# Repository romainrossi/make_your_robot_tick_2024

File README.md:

# Make Your Robot Tick 2024

Make Your Robot Tick, a robotics competition by ESIGELEC and Muthoot.

# Asking Questions about the Competition

As a participating Team, if you have a question about the RuleBook or other aspect of the competition, you have to fill an issue in this repository.
1. Go to [Issues](../../issues)  and check if your question is already answered
2. If not, create a new issue with the "New Issue" button, and fill-in the form of the "RuleBook question" template.
3. The organisation team will shortly answer your question. Question and answer will be available for all teams.

# Soon

Soon, all the information for this robotics competition will be available here.
Follow this repository to be notified !

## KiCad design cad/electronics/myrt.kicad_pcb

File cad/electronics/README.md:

# Make Your Robot Tick - Electronics CAD files

This directory contains a KiCAD project for the electronic boards used on the game field.

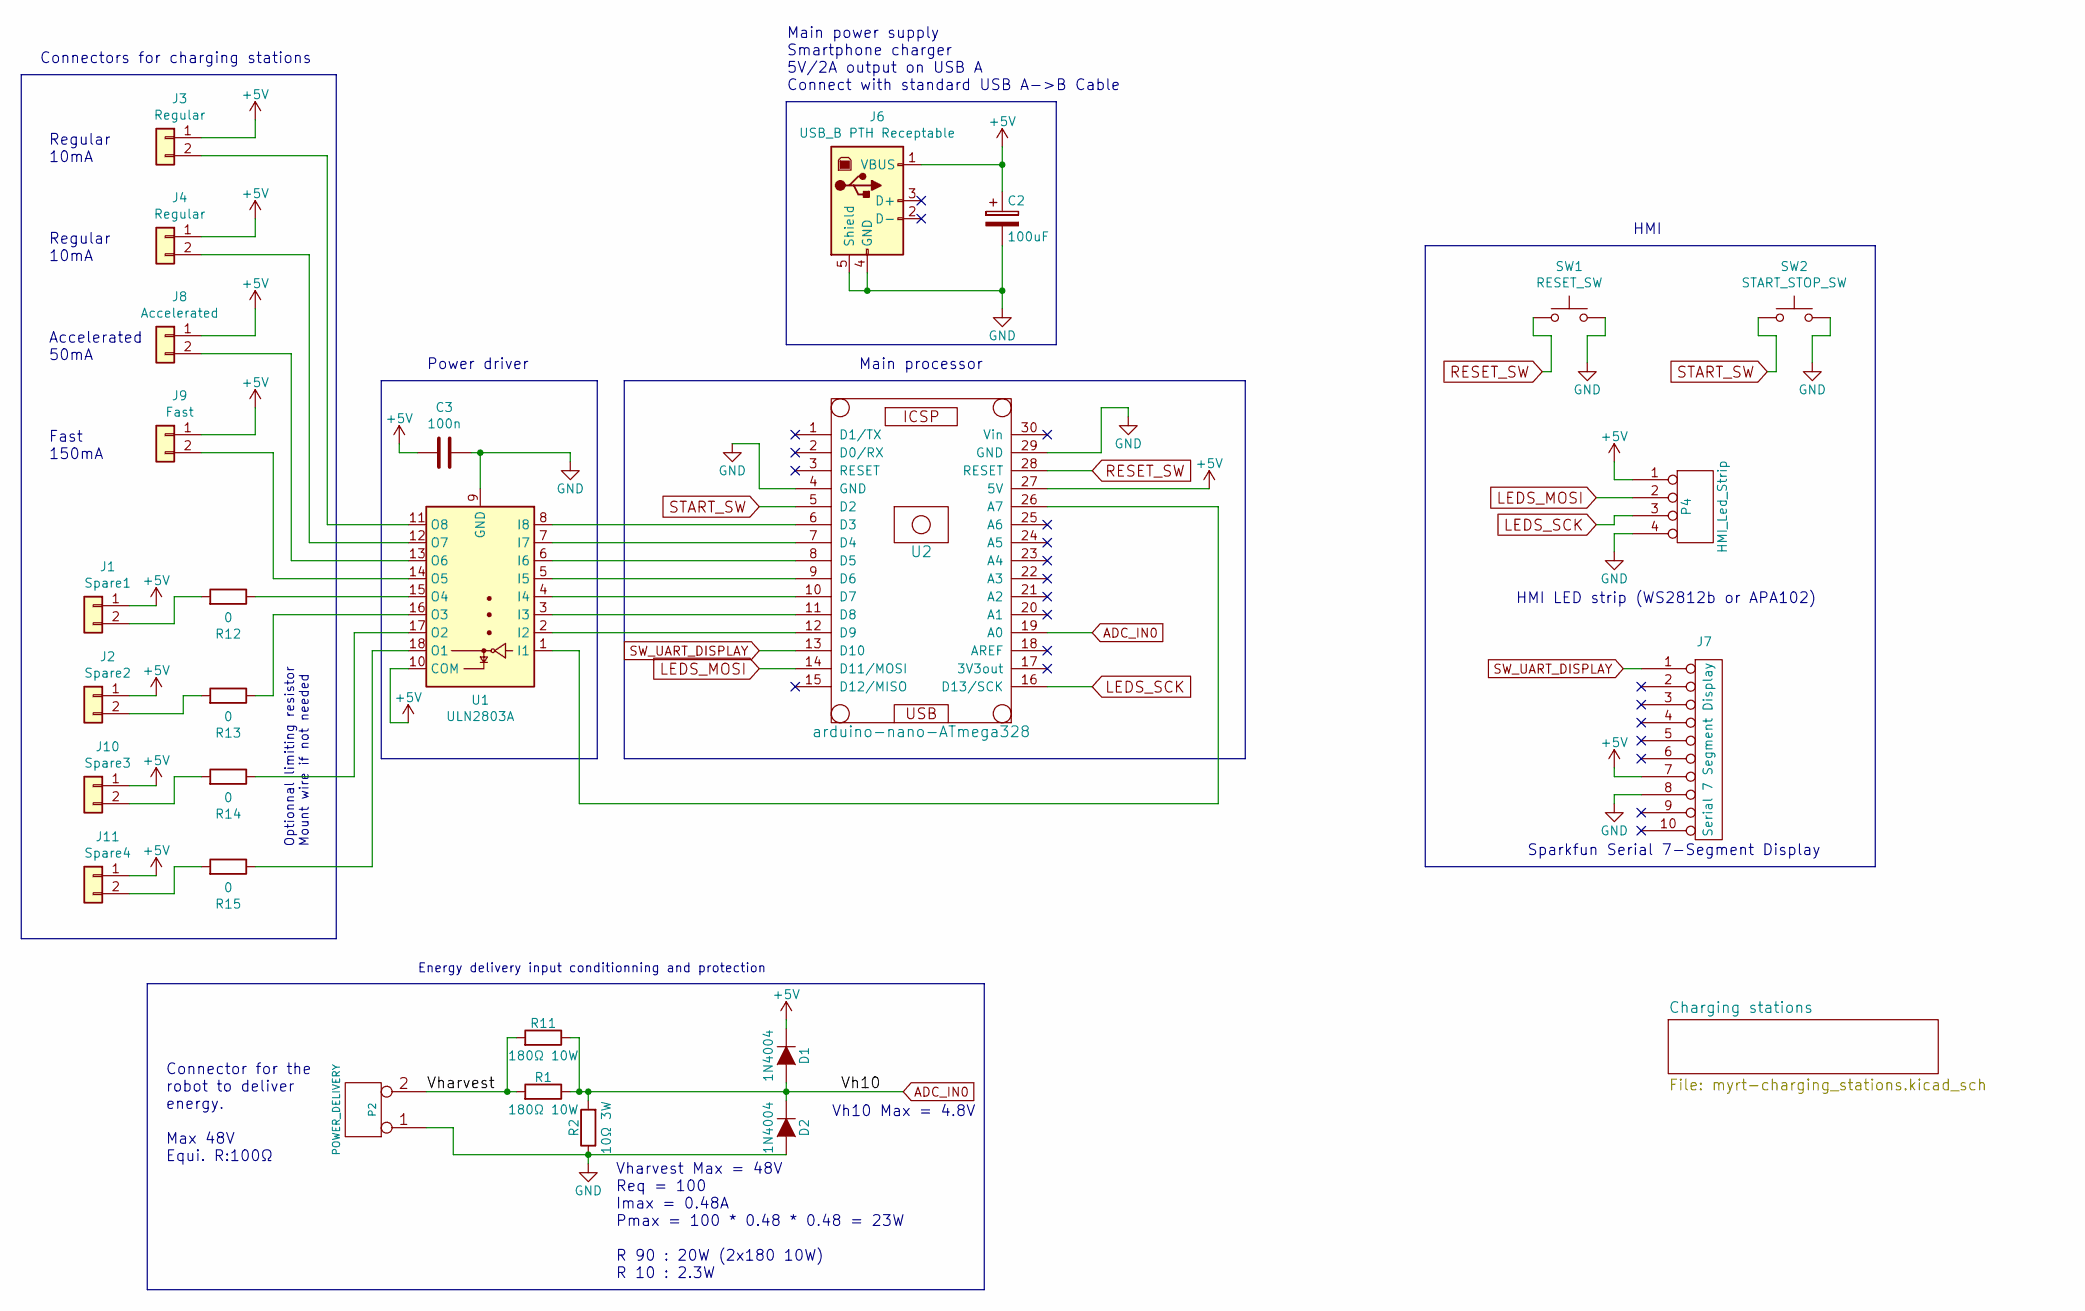
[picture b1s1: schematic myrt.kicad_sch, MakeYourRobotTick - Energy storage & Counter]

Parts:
C2: 100uF; CP_Radial_D10.0mm_P5.00mm
C3: 100n; C_Rect_L7.0mm_W2.5mm_P5.00mm
D1, D2: 1N4004; D_DO-41_SOD81_P12.70mm_Horizontal
J1: Spare1; PhoenixContact_MCV_1,5_2-G-3.5_1x02_P3.50mm_Vertical
J2: Spare2; PhoenixContact_MCV_1,5_2-G-3.5_1x02_P3.50mm_Vertical
J3, J4: Regular; PhoenixContact_MCV_1,5_2-G-3.5_1x02_P3.50mm_Vertical
J6: USB_B PTH Receptable; USB_B_OST_USB-B1HSxx_Horizontal
J7: Serial 7 Segment Display; PinSocket_1x10_P2.54mm_Vertical
J8: Accelerated; PhoenixContact_MCV_1,5_2-G-3.5_1x02_P3.50mm_Vertical
J9: Fast; PhoenixContact_MCV_1,5_2-G-3.5_1x02_P3.50mm_Vertical
J10: Spare3; PhoenixContact_MCV_1,5_2-G-3.5_1x02_P3.50mm_Vertical
J11: Spare4; PhoenixContact_MCV_1,5_2-G-3.5_1x02_P3.50mm_Vertical
P2: POWER_DELIVERY; PhoenixContact_MCV_1,5_2-G-3.5_1x02_P3.50mm_Vertical
P4: HMI_Led_Strip; PinSocket_1x04_P2.54mm_Vertical
R1, R11: 180Ω 10W; R_Axial_Power_L48.0mm_W12.5mm_P55.88mm
R2: 10Ω 3W; R_Axial_DIN0516_L15.5mm_D5.0mm_P25.40mm_Horizontal
R12, R13, R14, R15: 0; R_Axial_DIN0207_L6.3mm_D2.5mm_P15.24mm_Horizontal
SW1: RESET_SW; SW_PUSH-12mm_Wuerth-430476085716
SW2: START_STOP_SW; SW_PUSH-12mm_Wuerth-430476085716
U1: ULN2803A; DIP-18_W7.62mm_Socket_LongPads
U2: arduino-nano-ATmega328; Arduino_Nano

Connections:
+5V: C2.1, C3.2, D1.1 (K), J1.1, J2.1, J3.1, J4.1, J6.1 (VBUS), J7.7, J8.1, J9.1, J10.1, J11.1, P4.1, U1.10 (COM), U2.27 (5V)
/Vharvest: P2.2, R1.2, R11.2
ADC_IN0: D1.2 (A), D2.1 (K), R1.1, R2.2, R11.1, U2.19 (A0)
GND: C2.2, C3.1, D2.2 (A), J6.4 (GND), J6.5 (Shield), J7.8, P2.1, P4.4, R2.1, SW1.2, SW2.2, U1.9 (GND), U2.4 (GND), U2.29 (GND)
LEDS_MOSI: P4.2, U2.14 (D11/MOSI)
LEDS_SCK: P4.3, U2.16 (D13/SCK)
unnamed: J1.2, R12.2
unnamed: J2.2, R13.2
unnamed: J3.2, U1.11 (O8)
unnamed: J4.2, U1.12 (O7)
unnamed: J8.2, U1.13 (O6)
unnamed: J9.2, U1.14 (O5)
unnamed: J10.2, R14.2
unnamed: J11.2, R15.2
unnamed: R12.1, U1.15 (O4)
unnamed: R13.1, U1.16 (O3)
unnamed: R14.1, U1.17 (O2)
unnamed: R15.1, U1.18 (O1)
unnamed: U1.1 (I1), U2.26 (A7)
unnamed: U1.2 (I2), U2.12 (D9)
unnamed: U1.3 (I3), U2.11 (D8)
unnamed: U1.4 (I4), U2.10 (D7)
unnamed: U1.5 (I5), U2.9 (D6)
unnamed: U1.6 (I6), U2.8 (D5)
unnamed: U1.7 (I7), U2.7 (D4)
unnamed: U1.8 (I8), U2.6 (D3)
RESET_SW: SW1.1, U2.28 (RESET)
START_SW: SW2.1, U2.5 (D2)
SW_UART_DISPLAY: J7.1, U2.13 (D10)

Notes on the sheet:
Connector for the robot to deliver energy. Max 48V Equi. R:100Ω
Energy delivery input conditionning and protection
Optionnal limiting resistor Mount wire if not needed
Vharvest Max = 48V Req = 100 Imax = 0.48A Pmax = 100 * 0.48 * 0.48 = 23W R 90 : 20W (2x180 10W) R 10 : 2.3W
HMI
Main power supply Smartphone charger 5V/2A output on USB A Connect with standard USB A->B Cable
Power driver
Vh10 Max = 4.8V
Connectors for charging stations
Sparkfun Serial 7-Segment Display
HMI LED strip (WS2812b or APA102)
Accelerated 50mA
Regular 10mA
Fast 150mA
Main processor

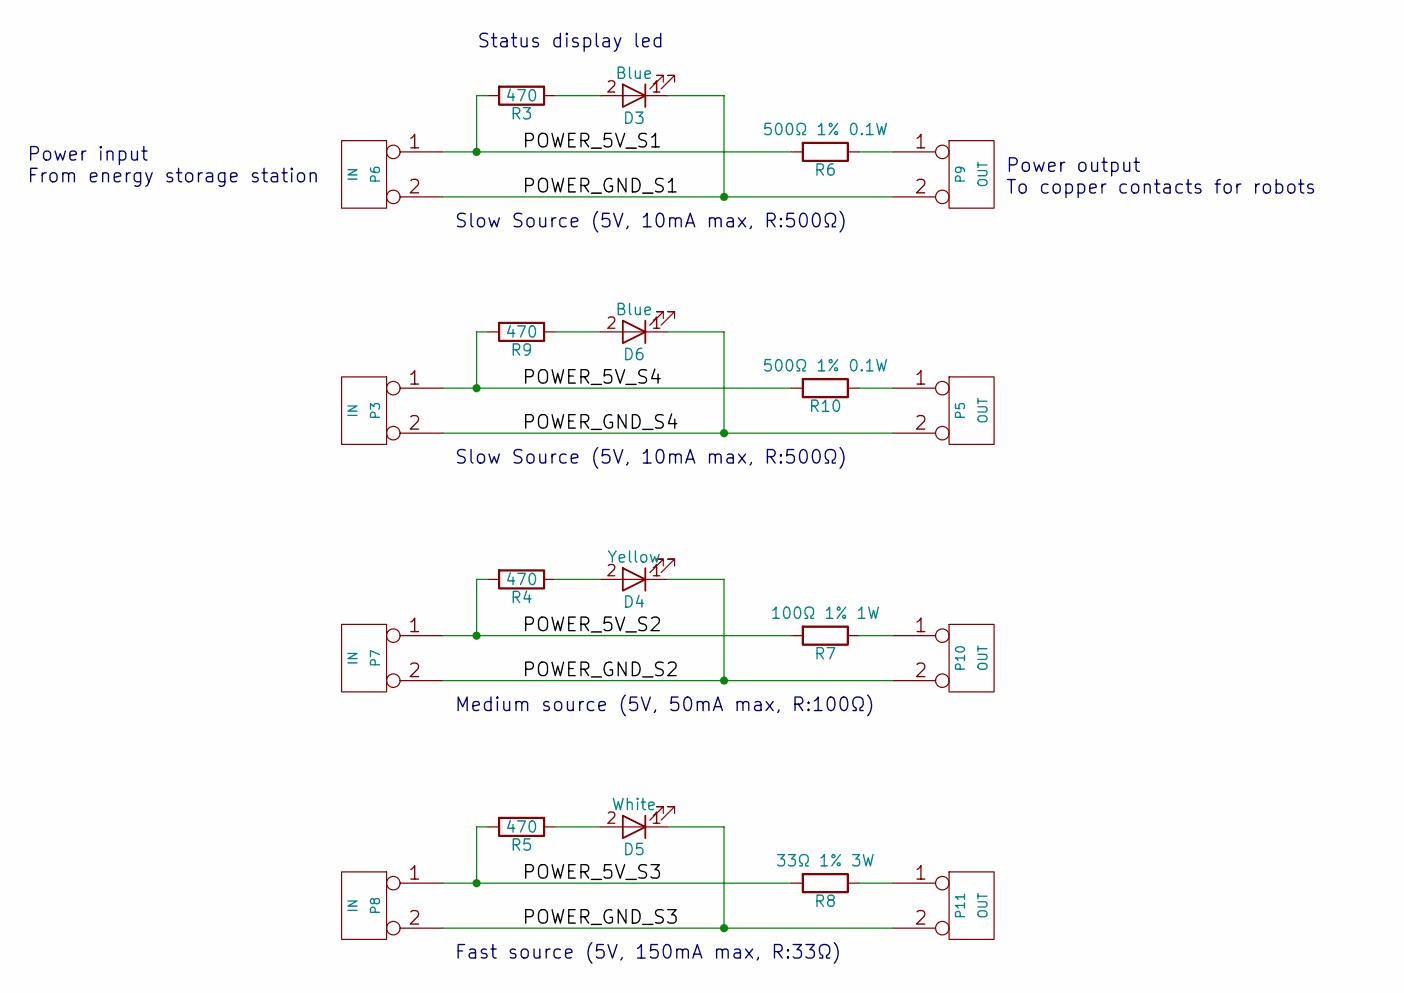
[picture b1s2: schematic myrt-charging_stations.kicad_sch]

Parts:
D3, D6: Blue; LED_D5.0mm
D4: Yellow; LED_D5.0mm
D5: White; LED_D5.0mm
P3, P6, P7, P8: IN; PhoenixContact_MCV_1,5_2-G-3.5_1x02_P3.50mm_Vertical
P5, P9, P10, P11: OUT; PinSocket_1x02_P2.54mm_Vertical
R3, R4, R5, R9: 470; R_Axial_DIN0207_L6.3mm_D2.5mm_P10.16mm_Horizontal
R6, R10: 500Ω 1% 0.1W; R_Axial_DIN0207_L6.3mm_D2.5mm_P15.24mm_Horizontal
R7: 100Ω 1% 1W; R_Axial_DIN0516_L15.5mm_D5.0mm_P25.40mm_Horizontal
R8: 33Ω 1% 3W; R_Axial_DIN0614_L14.3mm_D5.7mm_P25.40mm_Horizontal

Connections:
/Charging stations/POWER_5V_S1: P6.1, R3.2, R6.2
/Charging stations/POWER_5V_S2: P7.1, R4.2, R7.2
/Charging stations/POWER_5V_S3: P8.1, R5.2, R8.2
/Charging stations/POWER_5V_S4: P3.1, R9.2, R10.2
/Charging stations/POWER_GND_S1: D3.1 (K), P6.2, P9.2
/Charging stations/POWER_GND_S2: D4.1 (K), P7.2, P10.2
/Charging stations/POWER_GND_S3: D5.1 (K), P8.2, P11.2
/Charging stations/POWER_GND_S4: D6.1 (K), P3.2, P5.2
unnamed: D3.2 (A), R3.1
unnamed: D4.2 (A), R4.1
unnamed: D5.2 (A), R5.1
unnamed: D6.2 (A), R9.1
unnamed: P5.1, R10.1
unnamed: P9.1, R6.1
unnamed: P10.1, R7.1
unnamed: P11.1, R8.1

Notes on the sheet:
Slow Source (5V, 10mA max, R:500Ω)
Medium source (5V, 50mA max, R:100Ω)
Status display led
Power output To copper contacts for robots
Power input From energy storage station
Fast source (5V, 150mA max, R:33Ω)

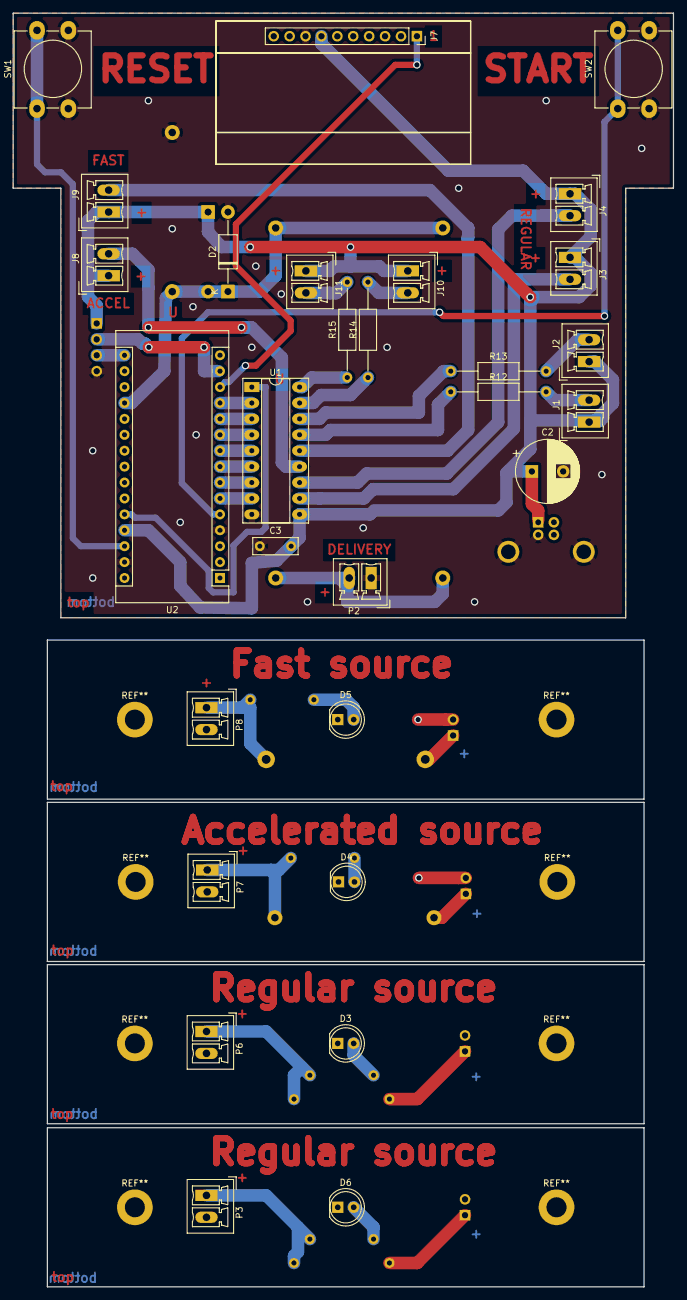
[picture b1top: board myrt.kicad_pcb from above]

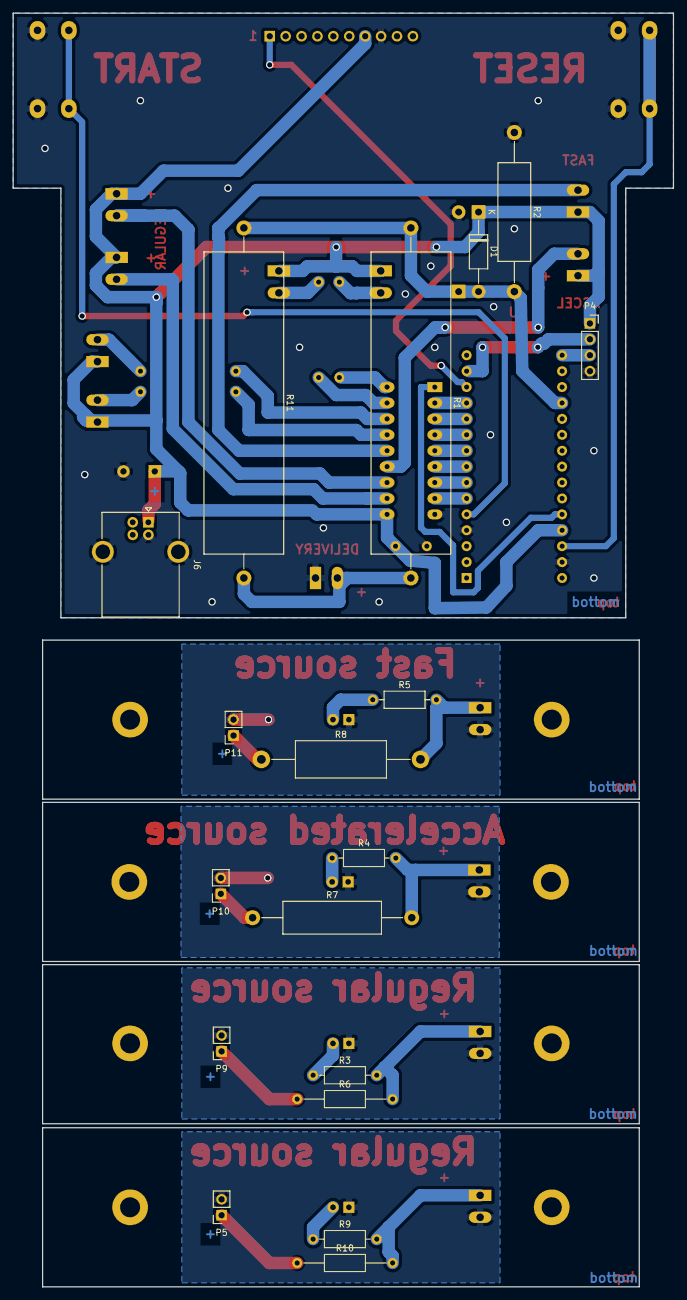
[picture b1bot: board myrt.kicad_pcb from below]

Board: 2 copper layers, 105.4 x 203.3 mm, 47 parts (18 on the bottom side), 45 nets.

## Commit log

2023-11-20 Adding Rulebook
2024-01-10 Update issue templates
2024-01-10 Update README.md
    Add question procedure
2024-01-10 Update README.md
    Correct link to issues
2024-01-10 Update rulebook-question.md
    Changed title prefix
2024-01-10 Update issue templates
    Added template for Final event question
2024-02-07 Added electronics schematics of Energy Storage Systems and Sources
2024-02-14 Updated source names to match with other documents (slow/medium/fast)
2024-02-14 Git ignore backups and generated output files
2024-03-05 Added new field plan and surface
2024-03-14 Updated Rulebook (new field plan)
2024-04-03 Corrected error "Expecting pts" on openning the Kicad PCB file (corrupted file)
